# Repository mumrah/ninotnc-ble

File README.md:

# NinoTNC BLE Expansion Board

This project brings robust and bi-directional Bluetooth connectivity to the
best amateur radio TNC on the market, the [NinoTNC](https://tarpn.net/t/nino-tnc/nino-tnc.html). This allows for the deployment of robust bi-directional APRS
at a low cost and in the DIY ham spirit.

The total cost for setting up an APRS mobile station using this project 
(excluding radio and antenna system) is around $80. 

* NinoTNC ($45 for DIY, more for pre-built)
* NinoBLE Expansion Board ($25 for pre-built, coming soon...)
* Custom TNC cable (free/cheap for DIY)
* APRS App (aprs.fi for iOS, APRSDroid for Android)

This project is experimental and should be considered as-is. The hardware and
firmware are open source licensed under the permissive MIT License.

# Features

* iOS and Android support
* Bi-directional APRS (receive and transmit)
* High-quality AFSK modulation, thanks to the NinoTNC
* USB powered using the USB-B connector on the NinoTNC
* Data logging to an on-board SD card
* Optional user-installed OLED display for packet information
* Pass-through mode for updating NinoTNC firmware

# Use Cases

## Mobile APRS

The most obvious and indeed the primary use case of this project. When set up
as described here, this board enables a very robust mobile APRS solution. Since
the NinoTNC is compatible with a wide range of 2m mobile radios (including
surplus commercial radios), the cost of the system can be kept low. 

The use of Bluetooth also allows for a "wireless" installation. There are no 
cables connected to the phone besides a charger. This allows for an arbitrary 
separation between the mobile phone and the TNC. The wireless range of the 
NinoBLE far exceeds any distance possible within a vehicle. 

## APRS Data Logging

The SD card located on the NinoBLE will log all packets sent and received.
This is quite useful when driving since logging in the APRS apps will
eventually roll off.

Each time the NinoBLE starts up, a new log file is created. This makes it
easy to find the most recent data, but also to retain the old data.

On-board data logging can also be useful for repeater operators who
occasionally have errant APRS traffic on their VHF repeaters. Logging
everything into the SD card makes it trivial to see who was accidentally
sending APRS traffic over the repeater.

## Portable APRS

If used with an HT, the NinoBLE can be used for portable APRS tracking. 
Since the APRS mobile apps use the phone's GPS, it is quite simple
to take this system into the field.

The same benefits of the Mobile APRS use case apply here. We can use 
inexpensive radios thanks to the high-quality DSP performed by the NinoTNC.

If the NinoBLE is equipped with the optional OLED screen, the NinBLE can be
used as a simple APRS receiver without a mobile phone.

## How it works

The primary function that this board adds to the NinoTNC is Bluetooth 
connectivity. There are many use cases for this besides APRS, but for now APRS 
is the focus of this project.

The expansion board is called the NinoBLE and connects physically to the NinoTNC
through the J5 header located under the USB to UART bridge. The NinoBLE board
replaces the USB to UART bridge that is normally installed on the TNC (at U4).

As KISS packets are received by the expansion board over Bluetooth, they are
decoded and forwarded to the UART interface. Similarly, when KISS data is
received over the UART, it is decoded and forwarded to the Bluetooth interface.

An optional SD card may be installed to capture the packets as they are sent andreceived.

## Hacking

The physical layout of the board is the only thing specific to the NinoTNC 
about this project. The electrical interface between the TNC and the expansion
board is 57600 baud UART and the data protocol used is KISS. This means that 
this project can be used to add Bluetooth to any KISS TNC that uses a UART.

The heart of this project is a RaspberryPi Pico W. Many of the GPIOs are unused,
so there is plenty of opportunity for expansion and tinkering.

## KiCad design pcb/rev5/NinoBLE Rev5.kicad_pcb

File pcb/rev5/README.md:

NinoTNC BLE rev5

The pogo pins (JLCPCB part number C5157269) are listed as Economy PCBA, but
really require Standard PCBA which is quite a bit more expensive. Also, the 
PCBA process for these pins is not super precise. All the boards I received 
had slight alignment issues. If you order this board, be sure to check the pins
for shorts.

In the next revision, I will source a different part for the pogo connector.

Files under the "fabrication" can be used for JLCPCB.

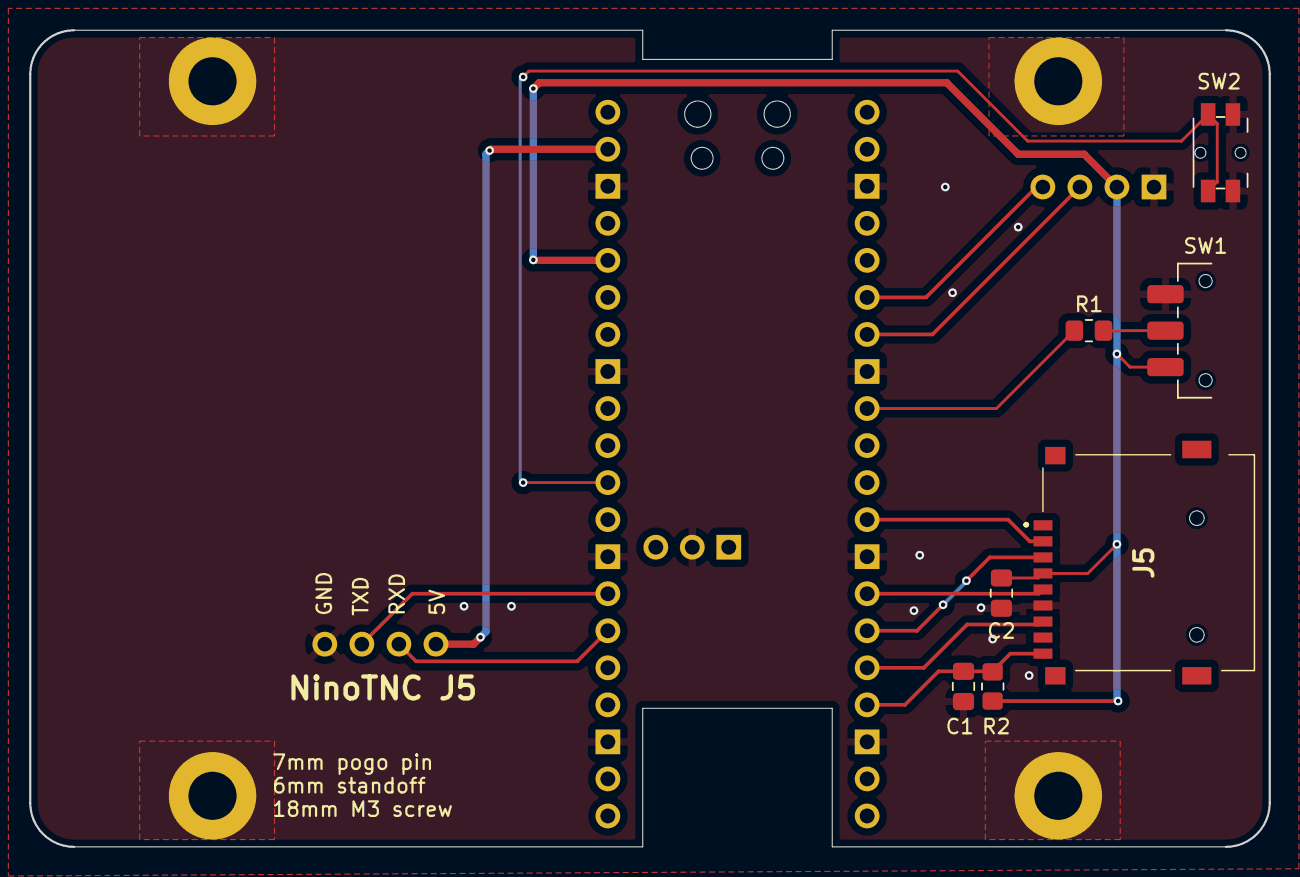
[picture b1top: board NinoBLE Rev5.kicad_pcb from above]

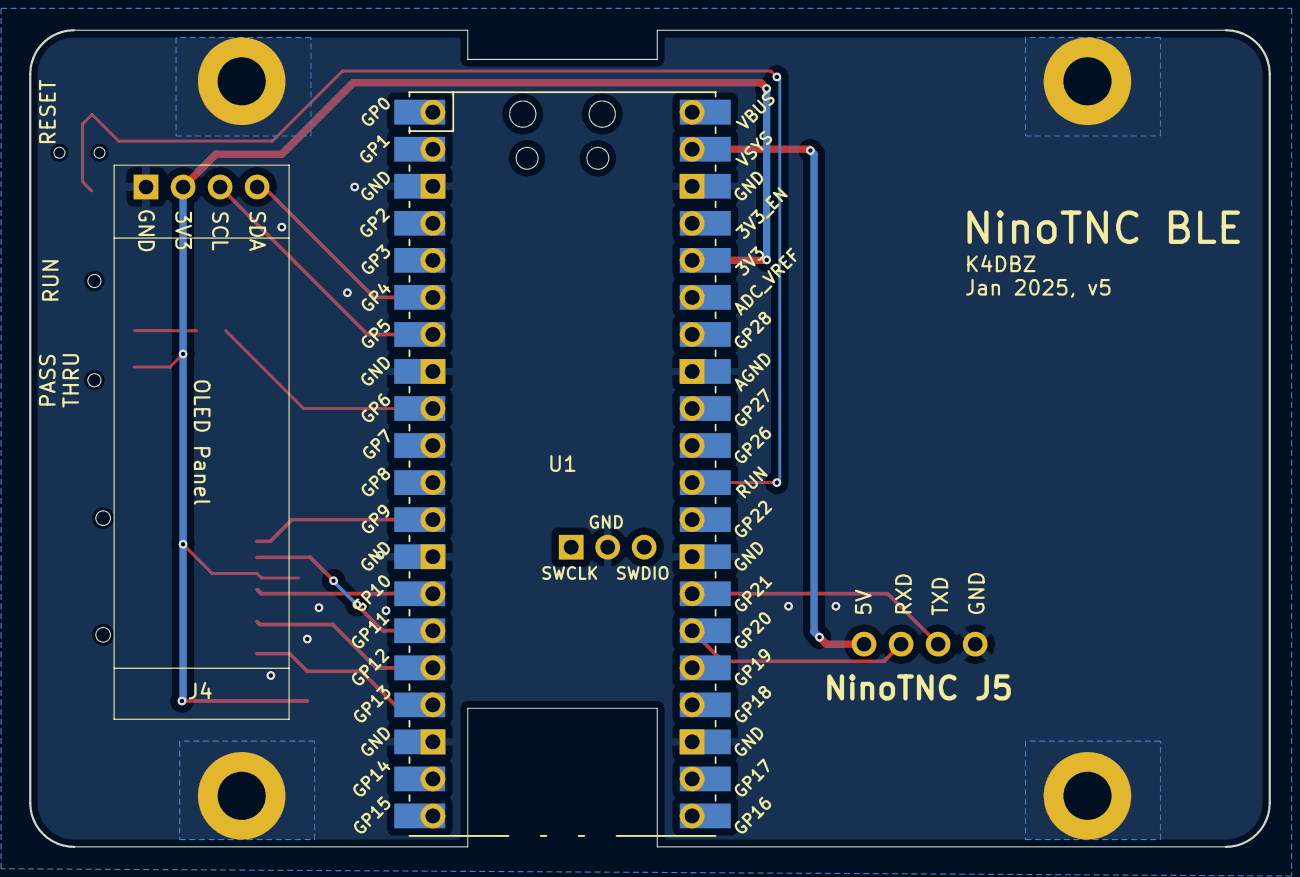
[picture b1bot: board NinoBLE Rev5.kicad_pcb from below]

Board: 2 copper layers, 85.0 x 56.0 mm, 14 parts (2 on the bottom side), 15 nets.

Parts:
C1, C2: C; C_0805_2012Metric_Pad1.18x1.45mm_HandSolder
J1, J2, J6, J7: Conn_01x01; Pin_D1.0mm_4.0mm_POGO
J3: Conn_01x01; NinoTNC_No_J5
J4: Conn_01x04; SSD1306-0.91-OLED-4pin-128x32
J5: TF-01A
R1, R2: 10k; R_0805_2012Metric_Pad1.20x1.40mm_HandSolder
SW1: SW_SPDT; SW_SPDT_CK_JS102011SAQN
SW2: SW_Push; Panasonic_EVQPUL_EVQPUC
U1: Pico; RPi_Pico_W_SMD_TH

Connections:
3V3: C2.1, J4.2, J5.4 (VDD), R2.2, SW1.1 (A), U1.36 (3V3)
5V: J7.1, U1.39 (VSYS)
/SPI1_CS: J5.2 (CD/DAT3), U1.12 (GPIO9)
/SPI1_RX: J5.7 (DAT0), U1.16 (GPIO12)
/SPI1_SCK: J5.5 (CLK), U1.14 (GPIO10)
/SPI1_TX: J5.3 (CMD), U1.15 (GPIO11)
GND: C1.2, C2.2, J1.1, J3.1, J4.1, J5.6 (VSS), SW1.3 (C), SW2.1, U1.3 (GND), U1.8 (GND), U1.13 (GND), U1.18 (GND), U1.23 (GND), U1.28 (GND), U1.33 (AGND), U1.38 (GND), U1.42 (GND)
MODE_SEL: R1.1, U1.9 (GPIO6)
unnamed: R1.2, SW1.2 (B)
RUN: SW2.2, U1.30 (RUN)
RXD: J6.1, U1.26 (GPIO20)
SCL: J4.3, U1.7 (GPIO5)
SDA: J4.4, U1.6 (GPIO4)
SD_CD: C1.1, J5.CD, R2.1, U1.17 (GPIO13)
TXD: J2.1, U1.27 (GPIO21)

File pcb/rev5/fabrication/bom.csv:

Designator,Footprint,Quantity,Value,LCSC Part #
"C1, C2",0805,2,C,C28233
"J1, J2, J6, J7",Pin_D1.0mm_4.0mm_POGO,4,Conn_01x01,C5157269
J3,NinoTNC_No_J5,1,Conn_01x01,
J4,SSD1306-0.91-OLED-4pin-128x32,1,Conn_01x04,
J5,TF-01A,1,TF-01A,C91145
"R1, R2",0805,2,10k,C17414
SW1,SW_SPDT_CK_JS102011SAQN,1,SW_SPDT,C221660
SW2,Panasonic_EVQPUL_EVQPUC,1,SW_Push,C79175
U1,RPi_Pico_W_SMD_TH,1,Pico,

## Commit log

2020-10-13 Sort of working, converting to 328pb next
2020-10-15 Things are working
2020-10-16 Remove debug code
2020-10-16 minor cleanup
2020-11-27 Compiling
2020-12-01 Fix timing issues, got software serial working
    Still no data from BLE
2020-12-02 Fix several state related issues
2021-06-10 Cleanup
2021-06-11 Fix some timing issues in reading from BM70
2021-06-12 More reliable serial reading from BM70
2021-06-15 checkin before timer removal
2021-06-15 Things are working!
    One issue was not tying RST to MCLR on the NinoTNC. Occasionally, when
    programming the atemga, some magic sequence of bytes was sent that caused
    the NinoTNC to go into programming mode and the program got corrupted. Oops!
2021-06-15 Free up some memory
2021-06-15 Add some validation on BLE data
2021-06-18 Use interrupt for Nino TX as well
2021-06-22 Use F strings
2021-06-24 Async blinks
2021-06-24 Add GIT_REV macro
2021-06-24 Add dirty tag for uncommitted changes
2021-07-08 Don't forget the connection handle when getting a disconnect
    This (hopefully) fixes a bug where the board gets stuck in a reset/reconnect loop
2023-02-13 Add license (CC-BY-SA)
2023-02-13 Add PCB schematic and update readme
2025-01-18 1.0 updates
2025-01-18 Rename src directory
2025-01-18 add pcb
2025-01-18 Add YT video to README.md
2025-01-18 Move video down a bit
2025-01-19 fixup rev5 pcb files
2025-07-02 Get things working with Packet Commander
    * Only decode AX.25 from KISS DATA frames
    * Add mutex to protect buffers shared by the two cores
    * Add guard against infinite loop in AX.25 decoder
    * Allow multiple KISS frames to be buffered instead of just one
